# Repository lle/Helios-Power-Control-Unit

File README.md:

# Helios Makerspace - PCU: Power Control Unit

## Short Description
Device that request a keycode from the user in order to power-up a tool in a Makerspace  

## Demonstration
https://www.youtube.com/watch?v=vD_NKFLX1eg

## Problem Statement
At Helios Makerspace, there is a number of dangerous tools (ei: CNC, table saws, metal lathe). Members should always the staff if they can use the machine. 

## Creating the PCU
The power control unit locks the power from a tool until the correct password has been inputted. Furthermore, the administrator can set timeouts amount between 15 minutes and 2 hours. When the timeout has been reached, the PCU will produce several waves of warning beep at 60, 30 and 10 seconds, before shutting down.

## About Version 2 (2018 Model)
At the beginning of 2018, a version #2 has been produced. It has 4 minor but important upgrade
* LCD screen is on the I2C line of the Arduino
* 2 different passwords: user password + admin password
* wiring have been crimped and shrink-wrapped
* a NEMA15 female socket has been added

#### Close up of LCD I2C Connector
The LCD I2C module has 4 pins (SDA, SCL, GND, +5V). So it has been labelled "D, C, -, +"
The connector labelle "1  7" is for the keypad. The connector has been labelled to avoid placing the cable reversed.

a

#### Close up of NEMA15 socket
A custom 3D printing part has been produced to allow the installation of the panel-mount socket. The model is available for download in the "mechanical" folder

#### Close up of the wrapped crimpped cable
The cables are first crimpped and then heat-shrink are used to isolate the exposed metal part of the quick-connect.

## Limitations
The current board design only support devices lower than 10 amps at constant current due to the PCB trace width.
Assuming the PCB is 1oz/ft^2, at 10A and trace width of 180 mils the PCB temperature will raise by 21 degrees celcius. I wasn't confortable allowing the PCB to raise too much.
If you wanted to have a PCB that supports 15A, you would need to manufacture a PCB at 2oz/ft^2. 
* Beware: if you manufacture a PCB for 15A, change the fuse+fuse clip. They are only rated for 10A 

## Known Issues
### Relay flicker on boot-up
On boot-up the Arduino will turn on pin D13 and consequently turn on the relay for a breif moment. That is un-safe for the purpose of this device. This is caused by the Arduino bootloader which raises the LED pin HIGH during boot. We have to make this project as portable as possible, so instead of touching the bootloader and asking everybody to reflash their arduino, I'm just going to issue a new PCB design which uses pin D12 for the relay.

### Hardware Patch
To fix this problem on the first manufactured PCB, we can bypass the relay into pin D12 instead of D13.
* First cut the D13 pin off the Arduino Nano
* Then, on the bottom of the PCB, solder a bypass wire to connect D13 to D12

## BOM
| Digikey               |                       |                                                                             |                    |                |           |
|-----------------------|-----------------------|-----------------------------------------------------------------------------|--------------------|----------------|-----------|
| Quantity              | Part Number           | Description                                                                 | Comment           | Unit Price CAD | Sub Total |
| 1                     | Z2616-ND              | RELAY GEN PURPOSE SPDT 16A 5V                                               |                    | 3.06           | 3.06      |
| 10                    | 311-3454-1-ND         | CAP CER 1UF 25V X7R 1206                                                    |                    | 0.137          | 1.37      |
| 1                     | NTD3055L104T4GOSCT-ND | MOSFET N-CH 60V 12A DPAK                                                    |                    | 0.95           | 0.95      |
| 10                    | 311-100KCRCT-ND       | RES SMD 100K OHM 1% 1/8W 0805                                               |                    | 0.031          | 0.31      |
| 10                    | 311-10.0CRCT-ND       | RES SMD 10 OHM 1% 1/8W 0805                                                 |                    | 0.031          | 0.31      |
| 10                    | RMCF0805JT150RCT-ND   | RES SMD 150 OHM 5% 1/8W 0805                                                |                    | 0.024          | 0.24      |
| 10                    | RMCF0805JT470RCT-ND   | RES SMD 470 OHM 5% 1/8W 0805                                                |                    | 0.024          | 0.24      |
| 1                     | 732-4988-1-ND         | LED AMBER CLEAR 1206 SMD                                                    |                    | 0.27           | 0.27      |
| 1                     | 732-5032-1-ND         | LED GREEN CLEAR 1206 SMD                                                    |                    | 0.24           | 0.24      |
| 1                     | 668-1458-ND           | AUDIO MAGNETIC INDICATOR 4-7V TH                                            |                    | 2.16           | 2.16      |
| 1                     | A98472-ND             | CONN BARRIER STRIP 2CIRC 0.325"                                             |                    | 1.33           | 1.33      |
| 1                     | A98473-ND             | CONN BARRIER STRIP 3CIRC 0.325"                                             |                    | 1.52           | 1.52      |
| 2                     | 486-2019-ND           | FUSE CLIP CARTRIDGE 10A PCB                                                 | WARNING 10A ONLY   | 0.14           | 0.28      |
| 1                     | RXEF050-2HFCT-ND      | PTC RESET FUSE 72V 500MA RADIAL                                             |                    | 0.62           | 0.62      |
| 2                     | 493-14520-1-ND        | CAP ALUM 1000UF 20% 16V SMD                                                 |                    | 1.3            | 2.6       |
| 1                     | F1728-ND              | FUSE GLASS 15A 250VAC 5X20MM                                                |                    | 0.46           | 0.46      |
| 1                     | SMBJ7.0A-FDICT-ND     | TVS DIODE 7VWM 12VC SMB                                                     |                    | 0.6            | 0.6       |
| 1                     | 102-2589-ND           | POWER SUPPLY SWITCHING 5V 2W                                                |                    | 17.78          | 17.78     |
| 1                     | 495-6464-ND           | VARISTOR DISC 14MM                                                          |                    | 0.74           | 0.74      |
| 1                     | 3314J-2-103ECT-ND     | TRIMMER 10K OHM 0.25W SMD                                                   |                    | 3.12           | 3.12      |
| 1                     | Q212-ND               | PWR ENT RCPT IEC320-C14                                                     |                    | 1.13           | 1.13      |
| 1                     | Q337-ND               | PWR ENT RCPT NEMA5-15 PANEL                                                 |                    | 1.13           | 1.13      |
|                       |                       |                                                                             |                    |                |           |
| Other Stores          |                       |                                                                             |                    |                |           |
| Quantity              | Description           | URL                                                                         | Customer Reference | Unit Price CAD | Sub Total |
| 1                     | Project Box           | https://addison-electronique.com/boitier-abs-257-x-190-x-82-mm.html         |                    | 13.99          | 13.99     |
| 1                     | Extension Cord        | https://addison-electronique.com/rallonge-electrique-16-3-sjtw-1-metre.html |                    | 2.99           | 2.99      |
| 1                     | Switch                | https://addison-electronique.com/interrupteur-a-levier-on-off-7807.html     |                    | 1.99           | 1.99      |
| 1                     | Switch Cover          | https://addison-electronique.com/couvert-pour-interrupteur-a-levier-vert-clair.html |            | 0.99           | 0.99      |
|                       |                       |                                                                             |                    |                |           |
| 1                     | LCD                   | http://bit.ly/2vsK9xS                                                       |                    | 2.49           | 2.49      |
| 1                     | Keypad                | http://bit.ly/2wrNNMV                                                       |                    | 1.60           | 1.60      |
|                       |                       |                                                                             |                    |                |           |
| 1                     | Arduino Nano          | https://www.sunfounder.com/board/arduino/nano.html                          |                    | 13.94          | 13.94     |
|                       |                       |                                                                             |                    |                |           |

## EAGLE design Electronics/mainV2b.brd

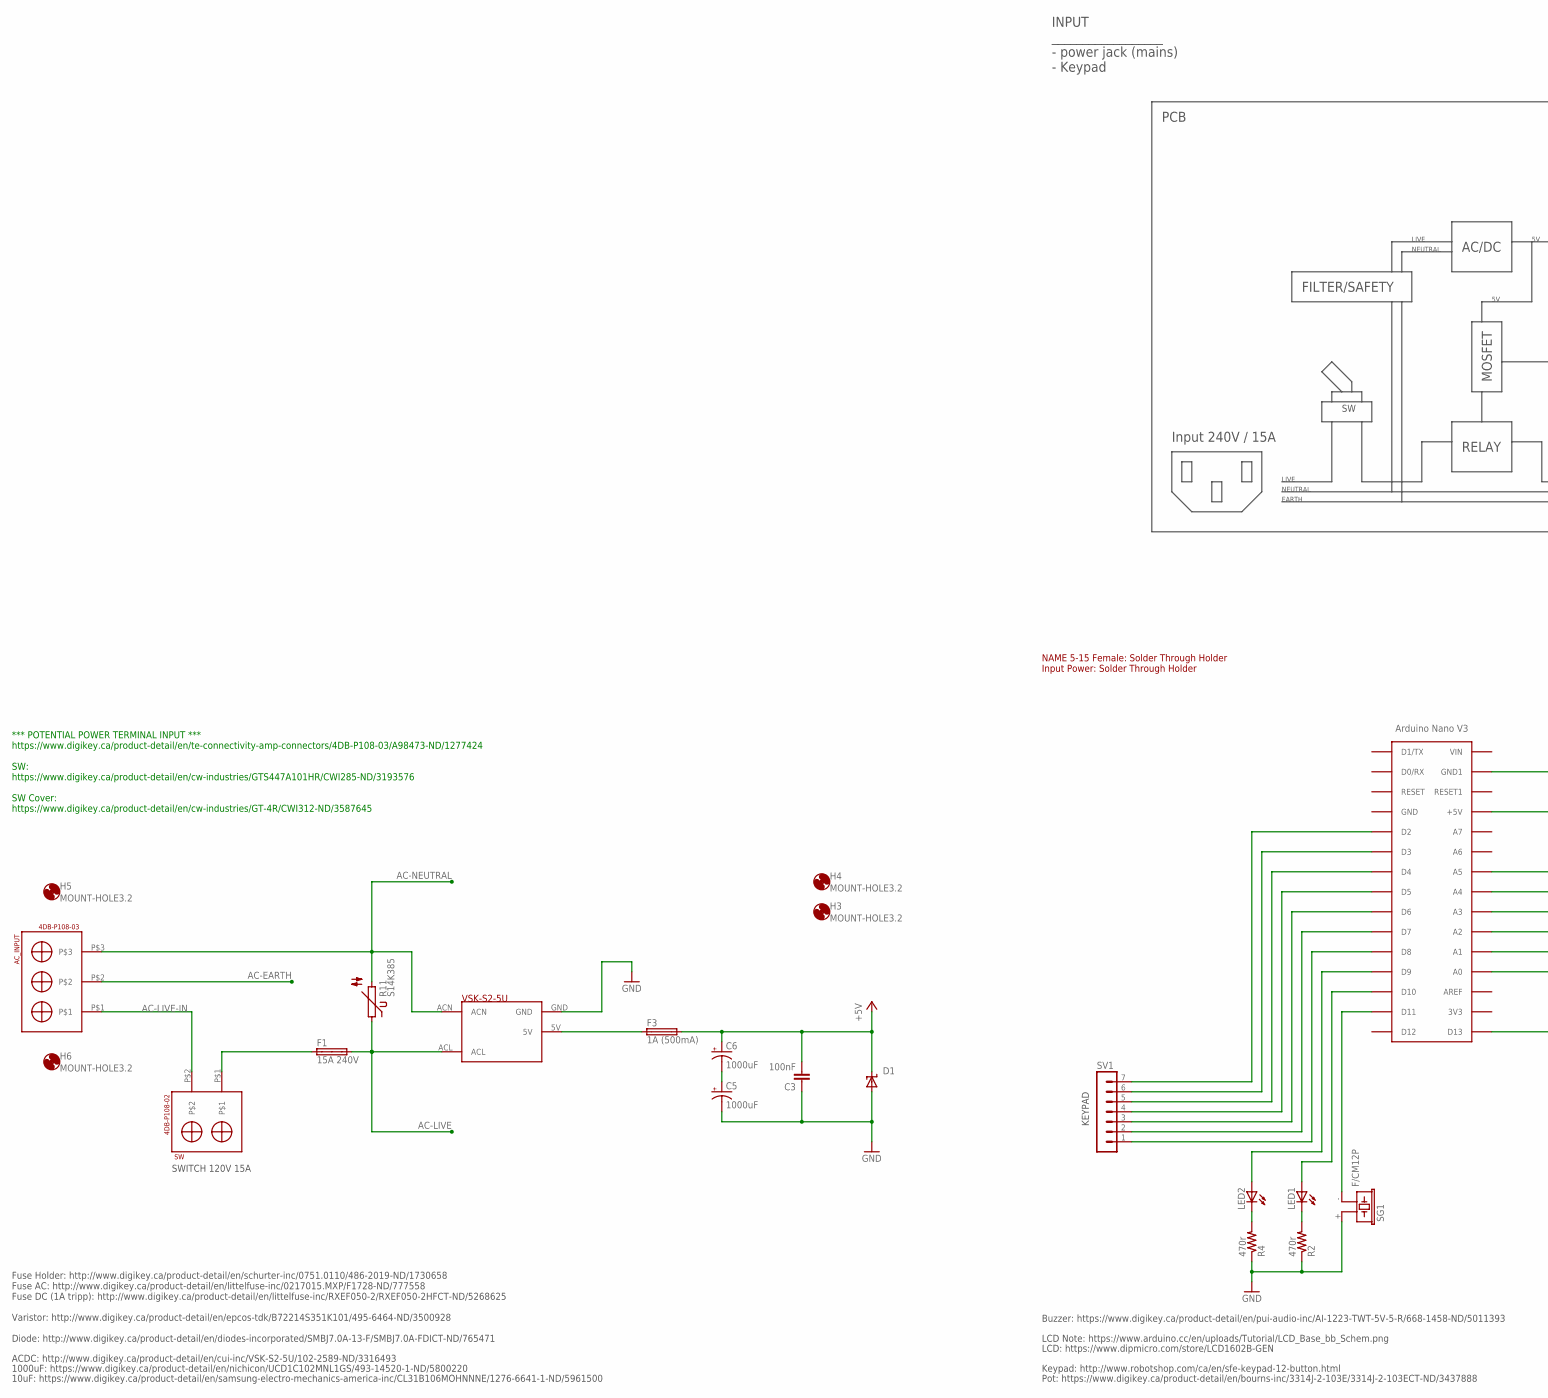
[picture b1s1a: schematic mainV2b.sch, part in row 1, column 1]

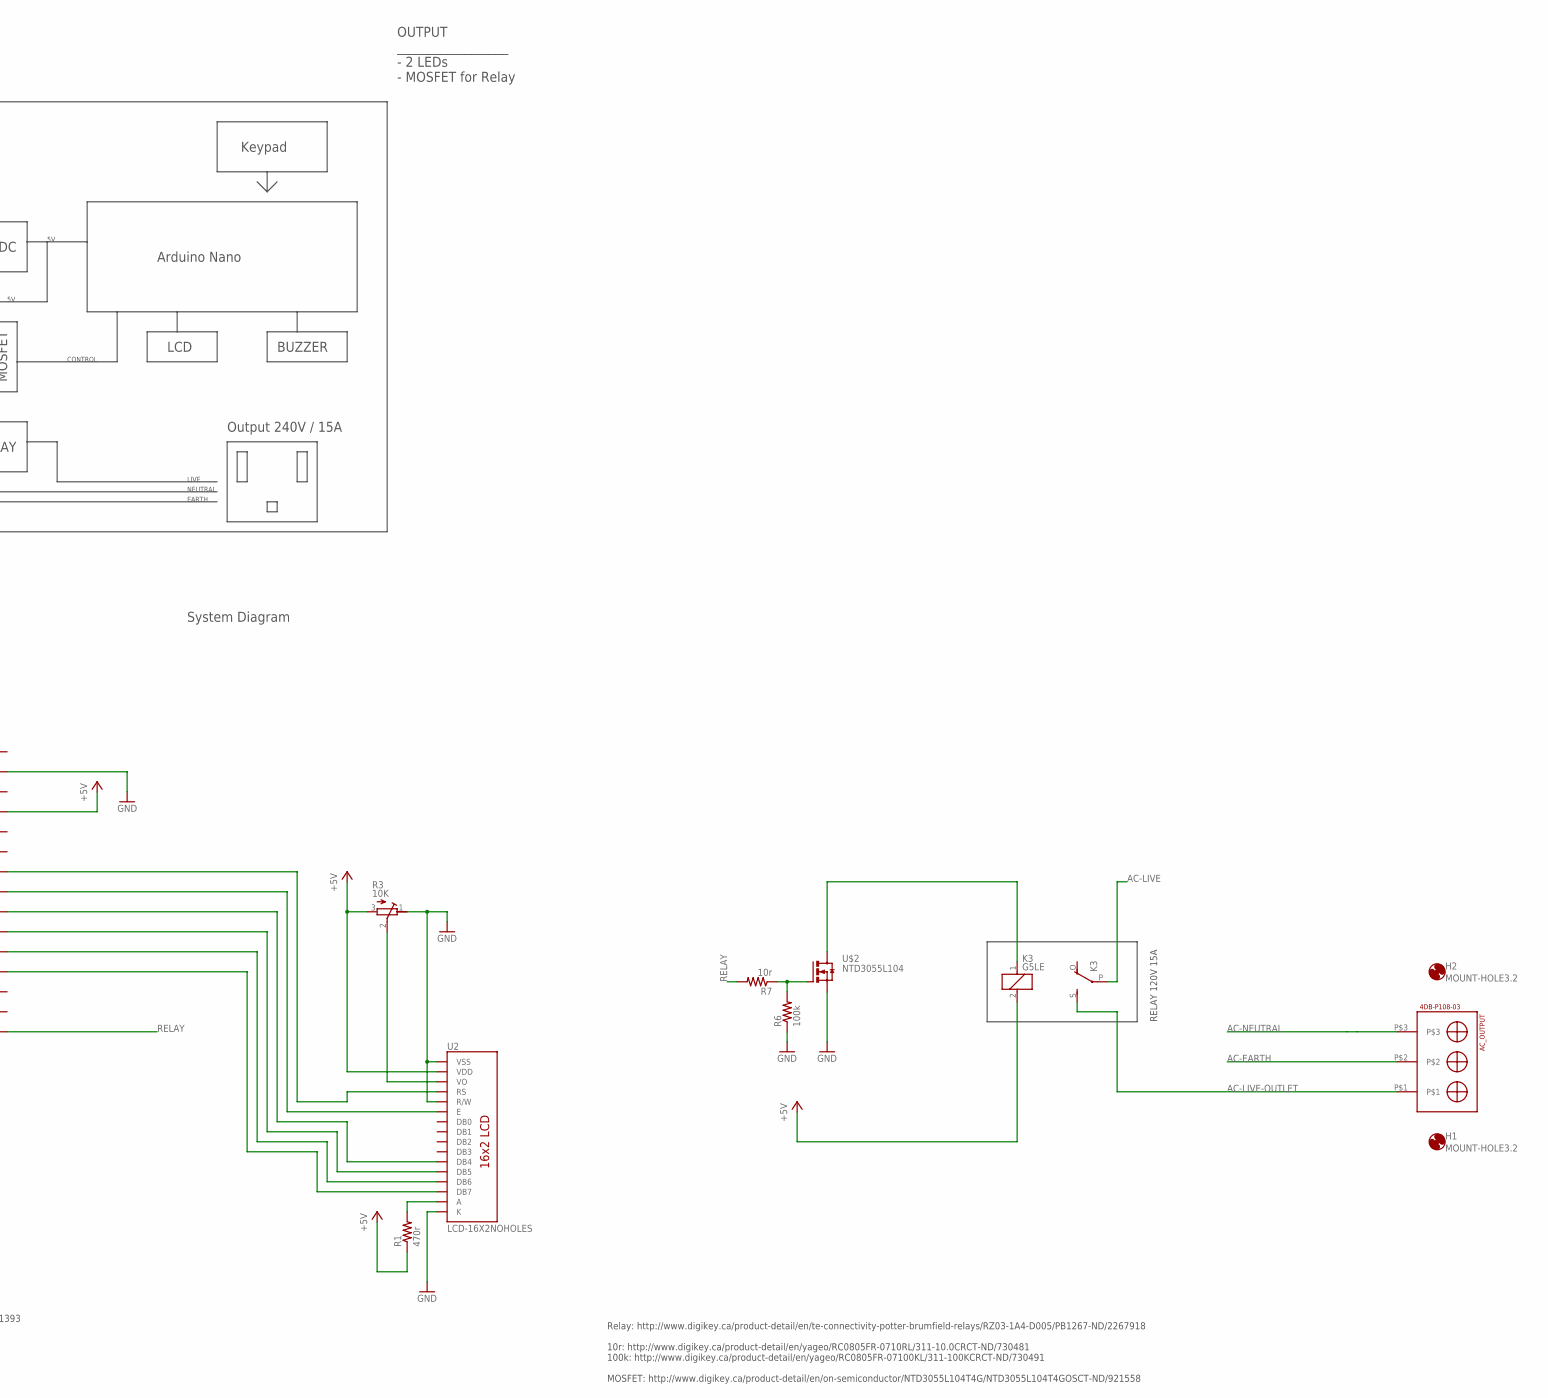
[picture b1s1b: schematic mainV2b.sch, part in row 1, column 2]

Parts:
AC_INPUT: 4DB-P108-03
AC_OUTPUT: 4DB-P108-03
C3: 100nF; C1206
C5, C6: 1000uF; UD-10X10_NICHICON
D1: SUPPRESSOR-SMBJ; SMBJ
F1: 15A 240V; SHK20L
F3: 1A (500mA); TE5
H1, H2, H3, H4, H5, H6: MOUNT-HOLE3.2; 3,2
K3: G5LE
LED1, LED2: LEDCHIPLED_1206; CHIPLED_1206
R1, R2, R4: 470r; M2012
R3: 10K; RTRIM3314G
R6: 100k; M2012
R7: 10r; M2012
R11: S14K385
SG1: F/CM12P
SV1: MA07-1
SW: 4DB-P108-02
U2: LCD-16X2NOHOLES; LCD-16X2_NOHOLESNOSILK
U$1: ARDUINONANO; PDIP-32
U$2: NTD3055L104; NTDV3055L104
U$4: VSK-2S-5U; VSK-S2-5U

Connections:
+5V: C3.2, C6.+, D1.C, F3.2, K3.2, R1.1, R3.3 (A), U2.2 (VDD), U$1.+5V
AC-EARTH: AC_INPUT.P$2, AC_OUTPUT.P$2
AC-LIVE: F1.2A, K3.P, R11.1, U$4.ACL
AC-LIVE-IN: AC_INPUT.P$1, SW.P$2
AC-LIVE-OUTLET: AC_OUTPUT.P$1, K3.S
AC-NEUTRAL: AC_INPUT.P$3, AC_OUTPUT.P$3, R11.2, U$4.ACN
GND: C3.1, C5.-, D1.A, R2.1, R3.1 (E), R4.1, R6.1, SG1.+ (1), U2.1 (VSS), U2.5 (R/W), U2.16 (K), U$1.GND1, U$2.3 (S), U$4.GND
unnamed: U2.4 (RS), U$1.A2 (A5)
unnamed: U2.6 (E), U$1.A3 (A4)
unnamed: U2.11 (DB4), U$1.A4 (A3)
unnamed: U2.12 (DB5), U$1.A5 (A2)
unnamed: U2.13 (DB6), U$1.A6 (A1)
unnamed: R6.2, R7.1, U$2.1 (G)
unnamed: U2.14 (DB7), U$1.A7 (A0)
unnamed: K3.1, U$2.4 (D)
unnamed: R3.2 (S), U2.3 (VO)
unnamed: R1.2, U2.15 (A)
unnamed: F1.1A, SW.P$1
unnamed: SV1.1, U$1.D8
unnamed: SV1.2, U$1.D7
unnamed: SV1.3, U$1.D6
unnamed: SV1.4, U$1.D5
unnamed: SV1.5, U$1.D4
unnamed: C5.+, C6.-
unnamed: F3.1, U$4.5V
unnamed: SV1.6, U$1.D3
unnamed: SV1.7, U$1.D2
unnamed: LED1.C, R2.2
unnamed: LED2.C, R4.2
unnamed: LED2.A, U$1.D9
unnamed: LED1.A, U$1.D10
unnamed: SG1.- (2), U$1.D11
RELAY: R7.2, U$1.D13

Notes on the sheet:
Relay: http://www.digikey.ca/product-detail/en/te-connectivity-potter-brumfield-relays/RZ03-1A4-D005/PB1267-ND/2267918 10r: http://www.digikey.ca/product-detail/en/yageo/RC0805FR-0710RL/311-10.0CRCT-ND/730481 100k: http://www.digikey.ca/product-detail/en/yageo/RC0805FR-07100KL/311-100KCRCT-ND/73049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
ACDC: http://www.digikey.ca/product-detail/en/cui-inc/VSK-S2-5U/102-2589-ND/3316493
Pot: https://www.digikey.ca/product-detail/en/bourns-inc/3314J-2-103E/3314J-2-103ECT-ND/3437888
1000uF: https://www.digikey.ca/product-detail/en/nichicon/UCD1C102MNL1GS/493-14520-1-ND/5800220
10uF: https://www.digikey.ca/product-detail/en/samsung-electro-mechanics-america-inc/CL31B106MOHNNNE/1276-6641-1-ND/5961500
Fuse Holder: http://www.digikey.ca/product-detail/en/schurter-inc/0751.0110/486-2019-ND/1730658 Fuse AC: http://www.digikey.ca/product-detail/en/littelfuse-inc/0217015.MXP/F1728-ND/777558 Fuse DC (1A tripp): http://www.digikey.ca/product-detail/en/littelfuse-inc/RXEF050-2/RXEF050-2HFCT-ND/5268625 V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
Keypad: http://www.robotshop.com/ca/en/sfe-keypad-12-button.html
LCD Note: https://www.arduino.cc/en/uploads/Tutorial/LCD_Base_bb_Schem.png
LCD: https://www.dipmicro.com/store/LCD1602B-GEN
*** POTENTIAL POWER TERMINAL INPUT *** https://www.digikey.ca/product-detail/en/te-connectivity-amp-connectors/4DB-P108-03/A98473-ND/1277424 SW: https://www.digikey.ca/product-detail/en/cw-industries/GTS447A101HR/CWI285-ND/3193576 SW Cover: https://www.digikey.ca/product-detail/en/cw-industries/GT-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
NAME 5-15 Female: Solder Through Holder Input Power: Solder Through Holder
System Diagram
PCB
Input 240V / 15A
Output 240V / 15A
AC/DC
RELAY
LIVE
NEUTRAL
EARTH
FILTER/SAFETY
Arduino Nano
MOSFET
CONTROL
Keypad
LCD
INPUT __________________ - power jack (mains) - Keypad
OUTPUT __________________ - 2 LEDs - MOSFET for Relay
BUZZER
KEYPAD
Buzzer: https://www.digikey.ca/product-detail/en/pui-audio-inc/AI-1223-TWT-5V-5-R/668-1458-ND/5011393
SWITCH 120V 15A
RELAY 120V 15A

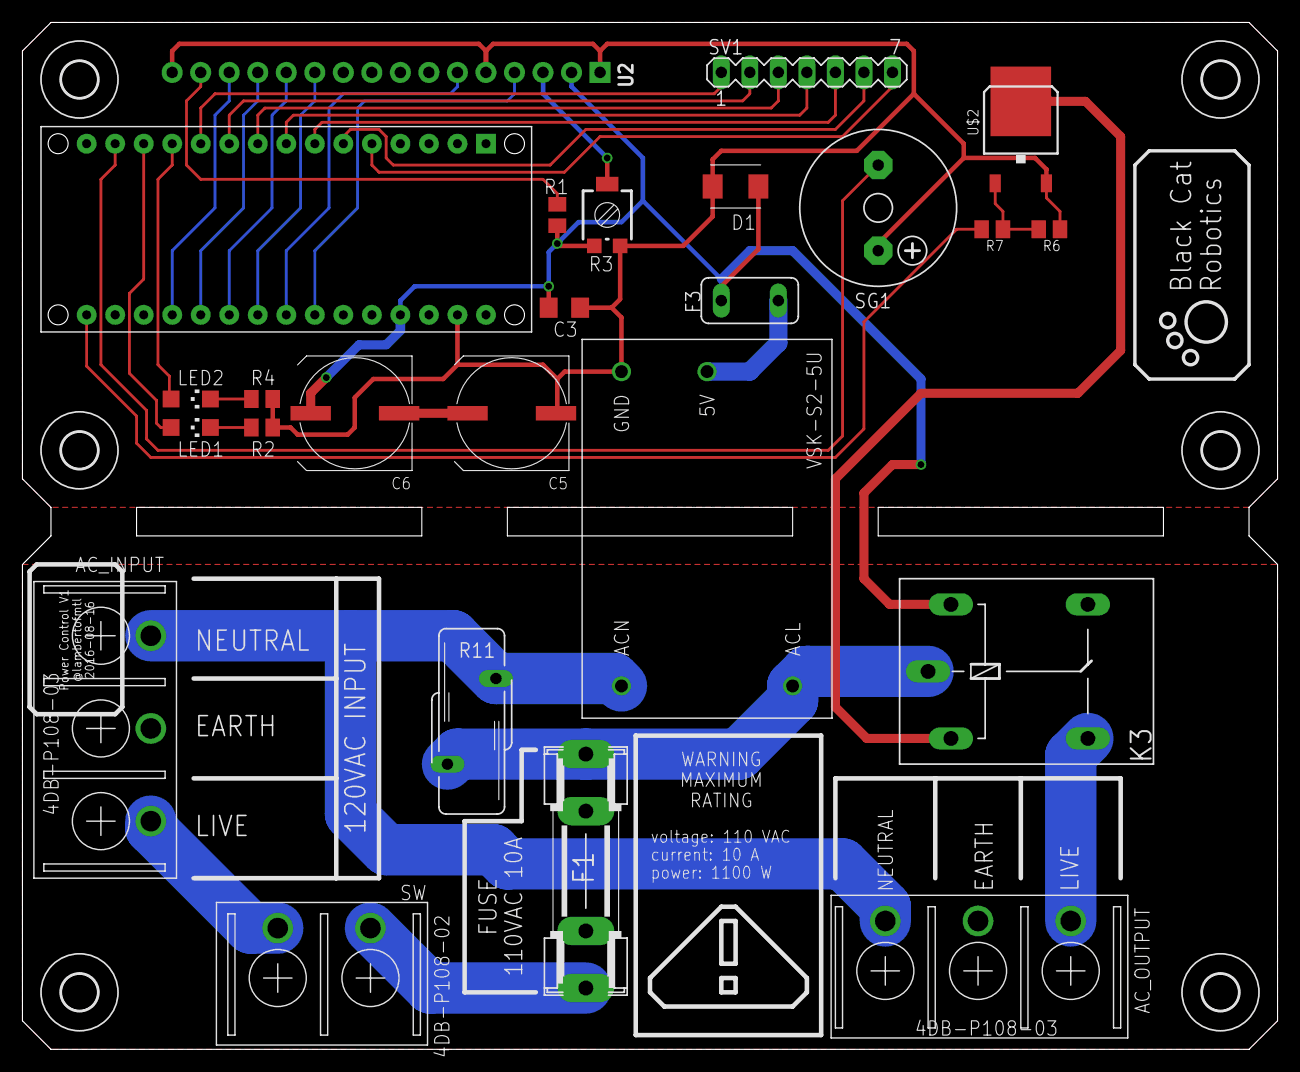
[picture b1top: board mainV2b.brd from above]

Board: 2 copper layers, 111.7 x 91.4 mm, 31 parts (0 on the bottom side), 33 nets.

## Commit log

2017-08-19 Push all the files
2017-08-19 added pic
2017-08-19 added new updated BOM
2017-08-19 correct BOM mistake
2017-08-19 Hardware Patch
    Since Pin D13 is raised HIGH during bootup due to the arduino bootloader, the relay turns on for a brief moment during boot-up. This is unsafe for the purpose of this device.
    So the relay control pin was moved from D13 to D12. Picture of the hardware patch has been included in the github readme
2017-08-19 Included instruction for Hardware Patch
    On boot-up the Arduino will turn on pin D13 and consequently turn on the relay for a breif moment. That is un-safe for the purpose of Tthis device.
    To fix this problem on the first manufactured PCB, we can bypass the relay into pin D12 instead of D13.
2017-08-21 Added Arduino
    Added Arduino
2017-08-24 Update README.md
    added required parts
2018-01-17 added pictures for documentation V2
2018-01-17 Updated readme
    added comment for version 2
2018-01-17 trying to reintroduce images into readme.md
2018-01-23 Updated missing files for V2
    Added folder for V2 firmware
    Added Mechanical parts that were 3D printed

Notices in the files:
parts and their libraries:
SparkFun-Displays: Licensing: Creative Commons ShareAlike 4.0 International - https://creativecommons.org/licenses/by-sa/4.0
